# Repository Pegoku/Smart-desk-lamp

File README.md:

# Smart Desk Lamp

This is a home assistant controlled CWWW desk lamp with capacitive touch buttons, made with ESPHome and ESP32-C3.

## Why I made it?

I made this project as I wanted to learn more about capacitive touch sensors and how to use them with ESPHome. I also wanted to make a simple desk lamp that could be controlled with Home Assistant.

## Features

- Capacitive touch buttons to control the brightness and color temperature of the LEDs.
- Home Assistant integration.

## Images

Final Build:

<details>
  <summary>Case/Assembly</summary>

</details>
<details>
  <summary>Main Schematic</summary>

</details>
<details>
  <summary>Main PCB</summary>

</details>

</details>
<details>
  <summary>LED Schematic</summary>

</details>
<details>
  <summary>LED PCB</summary>

</details>

## BOM

| Index | Part Number                        | What the item is for in your project | Description                         | Pack Quantity | ID                                                    | Unit Price | Total Price | Total (incl. VAT shipping, etc) |
| ----- | ---------------------------------- | ------------------------------------ | ----------------------------------- | ------------- | ----------------------------------------------------- | ---------- | ----------- | ------------------------------- |
| 1     | IQS7222A001QNR                     | Capacitive sensor                    | 9 CHANNEL MUTUAL / 8 SELF-CAPAC     | 2             | 1790-IQS7222A001QNRCT-ND                              | 0.82       | 1.64        | ~140$                            |
| 2     | ESP32-C3-WROOM-02-H4               | MCU                                  | RF TXRX MOD BT WIFI PCB TH SMD      | 1             | 1965-ESP32-C3-WROOM-02-H4CT-ND                        | 3.51       | 3.51        |                                 |
| 3     | IRM-20-24                          | PSU                                  | AC/DC CONVERTER 24V 22W             | 1             | 1866-3040-ND                                          | 9.20       | 9.20        |                                 |
| 4     | AP63203WU-7                        | 3.3V buck                            | IC REG BUCK 3.3V 2A TSOT23-6        | 2             | AP63203WU-7DICT-ND                                    | 0.71       | 1.42        |                                 |
| 5     | AL5802-7                           | Led driver                           | IC LED DRVR LIN PWM 120MA SOT26     | 5             | AL5802-7DICT-ND                                       | 0.23       | 1.15        |                                 |
| 6     | 2N7002                             | mosfet to drive the led drivers      | MOSFET N-CH 60V 280MA SOT23-3       | 3             | 4878-2N7002CT-ND                                      | 0.12       | 0.36        |                                 |
| 7     | GW JTLPS1.CM-HNKK-XX510-1-150-R33  | 2200K led                            | LED DURIS E2835 WHT 2200K 2835      | 10            | 475-GWJTLPS1.CM-HNKK-XX510-1-150-R33CT-ND             | 0.067      | 0.67        |                                 |
| 8     | GW JTLPS1.CM-JNKN-XX51-1-150-R33   | 6500K led                            | LED DURIS E2835 WHITE 6500K 2835    | 10            | 475-GWJTLPS1.CM-JNKN-XX51-1-150-R33CT-ND              | 0.067      | 0.67        |                                 |
| 9     | SRR5018-3R9Y                       | inductor                             | FIXED IND 3.9UH 2A 55 MOHM SMD      | 2             | 118-SRR5018-3R9YCT-ND                                 | 0.64       | 1.28        |                                 |
| 10    | 12mm LED Gooseneck                 | 12mm LED Gooseneck                   | 30 cm silver, Outer M10 – Outer M10 | 1             | https://es.aliexpress.com/item/1005007938186623.html  | 11.50      | 11.50       |                                 |
| 11    | 703W-00/53                         | Power Connector                      | PWR ENT RCPT IEC320-C14 PNL SLDR    | 1             | Q219-ND                                               | 1.54       | 1.54        |                                 |
| 12    | MF72-005D7                         | Inrush current limiter               | ICL 5 Ω 20% 2A 9 mm                 | 2             | 317-1148-ND                                           | 0.43       | 0.86        |                                 |
| 13    | M3x30 mm 4762                      | M3x30 mm 4762                        | M3x30 mm 4762                       | 1             | https://www.aliexpress.com/item/1005006453614010.html | 3.105      | 3.105       |                                 |
| 14    | M10 nut                            | M10 nut                              | M10 nut                             | 1             | https://www.aliexpress.com/item/1005007593861199.html | 3.0935     | 3.0935      |                                 |
| 15    | Soldering iron heatset insert tips | Soldering iron heatset insert tips   | Soldering iron heatset insert tips  | 1             | https://www.aliexpress.com/item/1005008493831823.html | 21.3785    | 21.3785     |                                 |
| 16    | M3x6 mm 4762                       | M3x6 mm 4762                         | M3x6 mm 4762                        | 1             | https://www.aliexpress.com/item/1005006453614010.html | 2.139      | 2.139       |                                 |
| 17    | Wood Filament                      | Wood Filament                        | Wood Filament                       | 0             | https://www.aliexpress.com/item/1005006685394618.html | 38.1685    | 0           |                                 |
| 18    | 30 cm JST XH 4P                    | 30 cm JST XH 4P                      | 30 cm JST XH 4P                     | 1             | https://www.aliexpress.com/item/1005008319201640.html | 2.5645     | 2.5645      |                                 |
| 19    | CL10A104KA8NNNC                    | Passive                              | CAP CER 0.1 µF 25 V X5R 0603        | 10            | 1276-1857-1-ND                                        | 0.028      | 0.28        |                                 |
| 20    | CL10A475KQ8NNNC                    | Passive                              | CAP CER 4.7 µF 6.3 V X5R 0603       | 10            | 1276-1045-1-ND                                        | 0.008      | 0.08        |                                 |
| 21    | CL10A225KQ8NNNC                    | Passive                              | CAP CER 2.2 µF 6.3 V X5R 0603       | 10            | 1276-1183-1-ND                                        | 0.032      | 0.32        |                                 |
| 22    | CL10A226MQ8NRNC                    | Passive                              | CAP CER 22 µF 6.3 V X5R 0603        | 5             | 1276-1193-1-ND                                        | 0.22       | 1.10        |                                 |
| 23    | CL10A104KA8NNNC                    | Passive                              | CAP CER 0.1 µF 25 V X5R 0603        | 10            | 1276-1857-1-ND                                        | 0.028      | 0.28        |                                 |
| 24    | CL05C101JB5NNNC                    | Passive                              | CAP CER 100 pF 50 V C0G/NP0 0402    | 10            | 1276-1025-1-ND                                        | 0.003      | 0.03        |                                 |
| 25    | 61300411121                        | Passive                              | CONN HEADER VERT 4POS 2.54 mm       | 2             | 732-5317-ND                                           | 0.17       | 0.34        |                                 |
| 26    | CRCW0603470MJPEAHR                 | Passive                              | RES SMD 470 MΩ 5% 1/10 W 0603       | 10            | 541-470MAHCT-ND                                       | 0.151      | 1.51        |                                 |
| 27    | RC0603FR-074K7L                    | Passive                              | RES 4.7 KΩ 1% 1/10 W 0603           | 10            | 311-4.70KHRCT-ND                                      | 0.009      | 0.09        |                                 |
| 28    | RC0603FR-071KL                     | Passive                              | RES 1 KΩ 1% 1/10 W 0603             | 10            | 311-1.00KHRCT-ND                                      | 0.009      | 0.09        |                                 |
| 29    | RC0603FR-0710KL                    | Passive                              | RES 10 KΩ 1% 1/10 W 0603            | 10            | 311-10.0KHRCT-ND                                      | 0.009      | 0.09        |                                 |
| 30    | PTS815SJM250SMTRLFS                | Esp32 buttons                        | SWITCH TACTILE SPST-NO 0.05 A 12 V  | 4             | CKN12215-1-ND                                         | 0.22       | 0.88        |                                 |
| 31    | PCB                                | PCB                                  | PCBs + stencil                      | 1             | jlcpcb.com                                            | 53.03      | 53.03       |                                 |
| 32    | ERJ-6GEY0R00V                      | 0 ohm jumper                         | RES SMD 0 OHM JUMPER 1/8W 0805      | 20            | P0.0ACT-ND                                            | 0.02360    | 0.59        |                                 |

## Configuration

Remember to set your secrets in [secrets.yaml](Code/secrets.example.yaml).

All firmware configuration lives in [code.yaml](Code/code.yaml):
PS: This configuration is for reference only, The final configuration will be for the ESP32-S2. You'll also have to configure the devices you want to control in Home Assistant.

```yaml
esphome:
  name: desklight
  friendly_name: desklight

esp32:
  board: esp32-c3-devkitm-1
  framework:
    type: arduino

# Enable logging
logger:

# Enable Home Assistant API
api:
  encryption:
    key: !secret api_key

ota:
  - platform: esphome
    password: !secret ota_password

wifi:
  ssid: !secret wifi_ssid
  password: !secret wifi_password

  # Enable fallback hotspot (captive portal) in case wifi connection fails
  ap:
    ssid: "desklight Fallback Hotspot"
    password: "wHjqyQOLnaPa"

i2c:
  sda: GPIO6
  scl: GPIO7
  frequency: 800kHz
  scan: true

mpr121:
  id: mpr121_component
  address: 0x5A
  touch_debounce: 1
  release_debounce: 1
  touch_threshold: 10
  release_threshold: 7

binary_sensor:
  - platform: mpr121
    id: touch_key0
    channel: 0
    name: "Touch Key 0"
    touch_threshold: 12
    release_threshold: 6

light:
  - platform: cwww
    name: "Livingroom Lights"
    cold_white: WLight
    warm_white: CLight
    cold_white_color_temperature: 6500 K
    warm_white_color_temperature: 2200 K
    constant_brightness: true

output:
  - platform: ledc
    id: WLight
    pin: GPIO4
    frequency: 1000 Hz
  - platform: ledc
    id: CLight
    pin: GPIO5
    frequency: 1000 Hz

captive_portal:
```

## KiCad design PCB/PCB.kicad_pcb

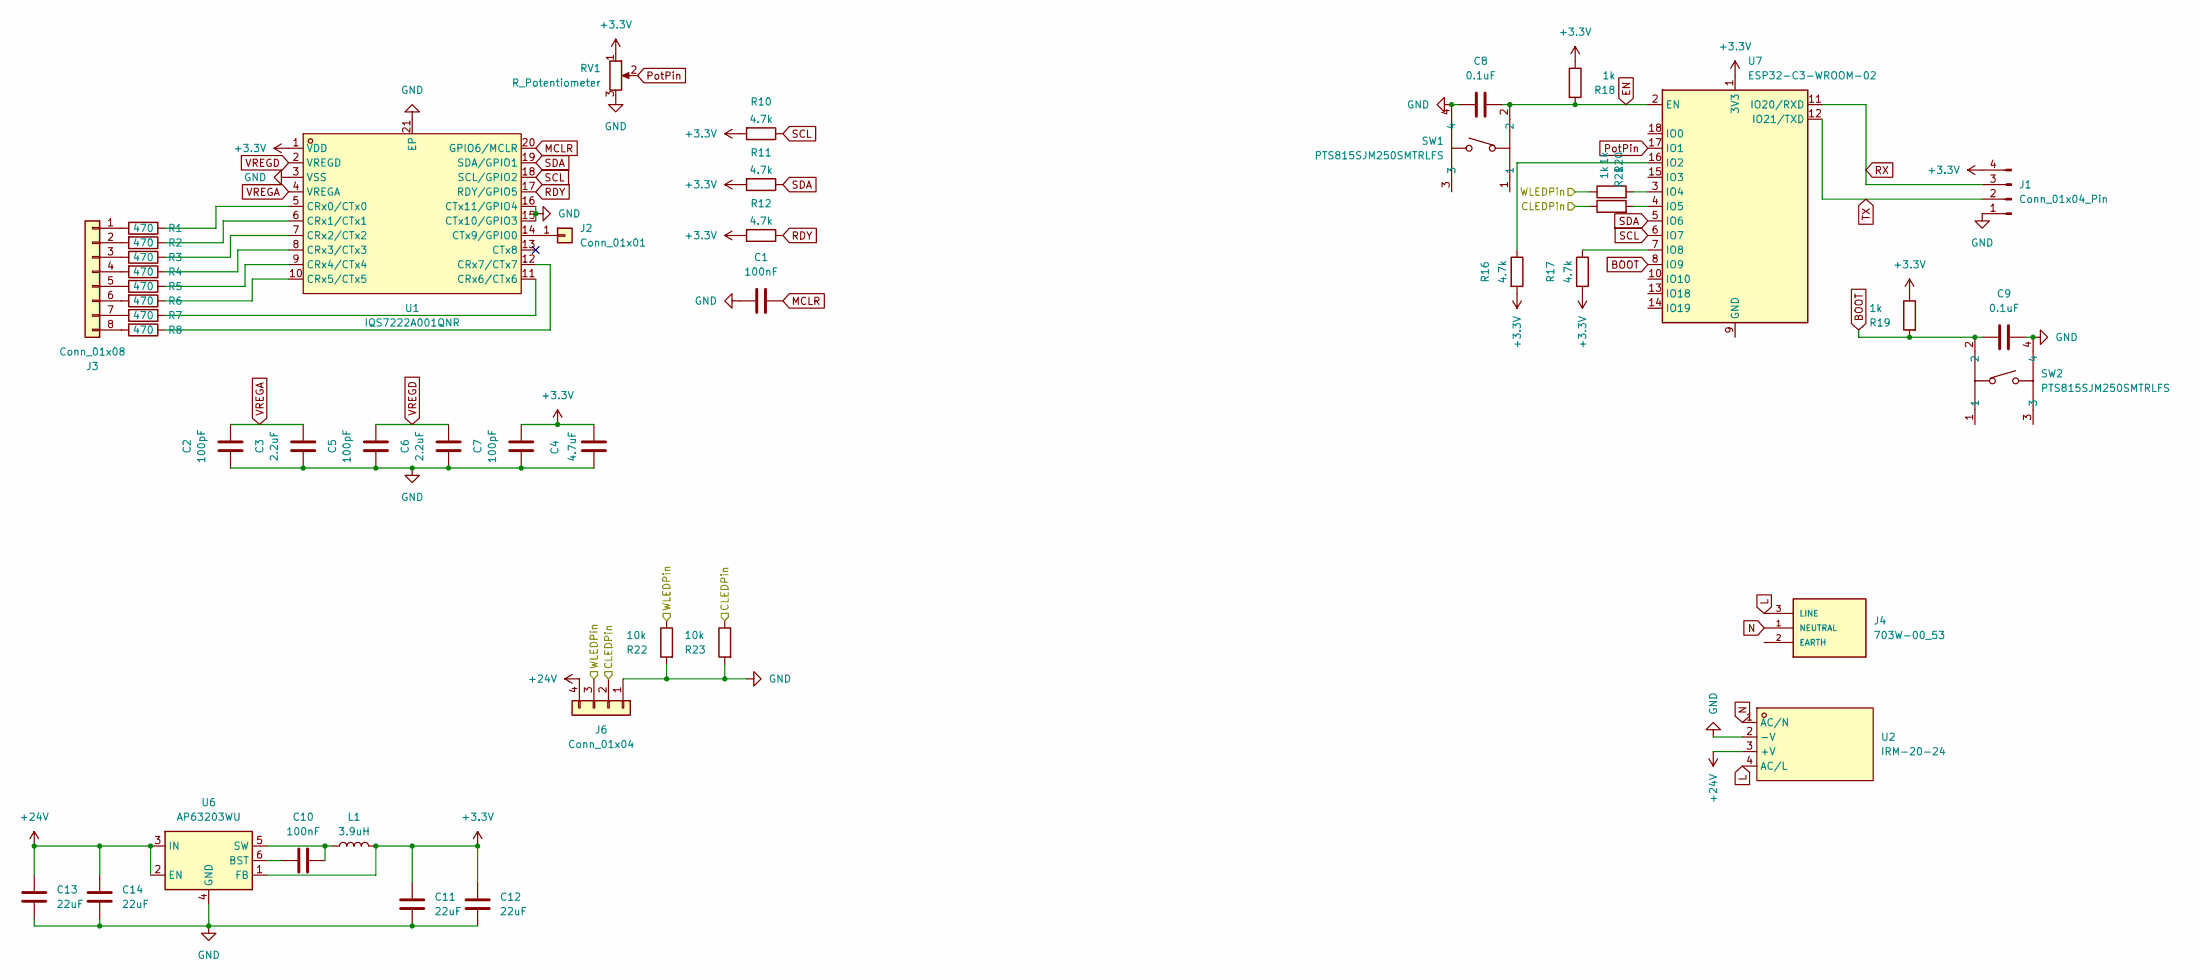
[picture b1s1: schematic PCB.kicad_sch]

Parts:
C1, C10: 100nF; C_0603_1608Metric
C2, C5, C7: 100pF; C_0603_1608Metric
C3, C6: 2.2uF; C_0603_1608Metric
C4: 4.7uF; C_0603_1608Metric
C8, C9: 0.1uF; C_0603_1608Metric
C11, C12, C13, C14: 22uF; C_0603_1608Metric
J1: Conn_01x04_Pin; PinHeader_1x04_P2.54mm_Vertical
J2: Conn_01x01; PinHeader_1x01_P2.54mm_Vertical
J3: Conn_01x08; TouchSlider-8_50x20mm
J4: 703W-00_53; QUALTEK_703W-00_53
J6: Conn_01x04; JST_XH_B4B-XH-AM_1x04_P2.50mm_Vertical
L1: 3.9uH; IND-SMD_L5.8-W5.8
R1, R2, R3, R4, R5, R6, R7, R8: 470; R_0603_1608Metric
R10, R11, R12, R16, R17: 4.7k; R_0603_1608Metric
R18, R19, R20, R21: 1k; R_0603_1608Metric
R22, R23: 10k; R_0603_1608Metric
RV1: R_Potentiometer; PinHeader_1x03_P2.54mm_Horizontal
SW1, SW2: PTS815SJM250SMTRLFS; KEY-SMD_4P-L4.2-W3.25-P2.15-TL; LCSC Part C2689510
U1: IQS7222A001QNR; WQFN-20_L3.0-W3.0-P0.40-BL-EP1.7; LCSC Part C3827627
U2: IRM-20-24; PWRM-TH_IRM-20-24; LCSC Part C194964
U6: AP63203WU; TSOT-23-6
U7: ESP32-C3-WROOM-02

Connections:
+3.3V: C4.2, C7.2, C11.2, C12.2, J1.4, L1.2, R10.2, R11.2, R12.2, R16.2, R17.2, R18.1, R19.1, RV1.1, U1.1 (VDD), U6.1 (FB), U7.1 (3V3)
+24V: C13.2, C14.2, J6.4, U2.3 (+V), U6.2 (EN), U6.3 (IN)
/Main PCB/CLEDPin: J6.2, R21.1, R23.1
/Main PCB/WLEDPin: J6.3, R20.1, R22.1
BOOT: C9.1, R19.2, SW2.2, U7.8 (IO9)
EN: C8.1, R18.2, SW1.2, U7.2 (EN)
GND: C1.1, C2.1, C3.1, C4.1, C5.1, C6.1, C7.1, C8.2, C9.2, C11.1, C12.1, C13.1, C14.1, J1.1, J6.1, R22.2, R23.2, RV1.3, SW1.4, SW2.4, U1.3 (VSS), U1.15 (CTx10/GPIO3), U1.16 (CTx11/GPIO4), U1.21 (EP), U2.2 (-V), U6.4 (GND)
L: J4.3 (LINE), U2.4 (AC/L)
MCLR: C1.2, U1.20 (GPIO6/MCLR)
N: J4.1 (NEUTRAL), U2.1 (AC/N)
unnamed: J2.1, U1.14 (CTx9/GPIO0)
unnamed: J3.1, R1.2
unnamed: J3.2, R2.2
unnamed: J3.3, R3.2
unnamed: J3.4, R4.2
unnamed: J3.5, R5.2
unnamed: J3.6, R6.2
unnamed: J3.7, R7.2
unnamed: J3.8, R8.2
unnamed: R1.1, U1.5 (CRx0/CTx0)
unnamed: R2.1, U1.6 (CRx1/CTx1)
unnamed: R3.1, U1.7 (CRx2/CTx2)
unnamed: R4.1, U1.8 (CRx3/CTx3)
unnamed: R5.1, U1.9 (CRx4/CTx4)
unnamed: R6.1, U1.10 (CRx5/CTx5)
unnamed: R7.1, U1.11 (CRx6/CTx6)
unnamed: R8.1, U1.12 (CRx7/CTx7)
unnamed: C10.1, U6.6 (BST)
unnamed: C10.2, L1.1, U6.5 (SW)
unnamed: U7.9 (GND), U7.19 (GND)
unnamed: R16.1, U7.16 (IO2)
unnamed: R20.2, U7.3 (IO4)
unnamed: R21.2, U7.4 (IO5)
unnamed: R17.1, U7.7 (IO8)
PotPin: RV1.2, U7.17 (IO1)
RDY: R12.1, U1.17 (RDY/GPIO5)
RX: J1.3, U7.11 (IO20/RXD)
SCL: R10.1, U1.18 (SCL/GPIO2), U7.6 (IO7)
SDA: R11.1, U1.19 (SDA/GPIO1), U7.5 (IO6)
TX: J1.2, U7.12 (IO21/TXD)
VREGA: C2.2, C3.2, U1.4 (VREGA)
VREGD: C5.2, C6.2, U1.2 (VREGD)

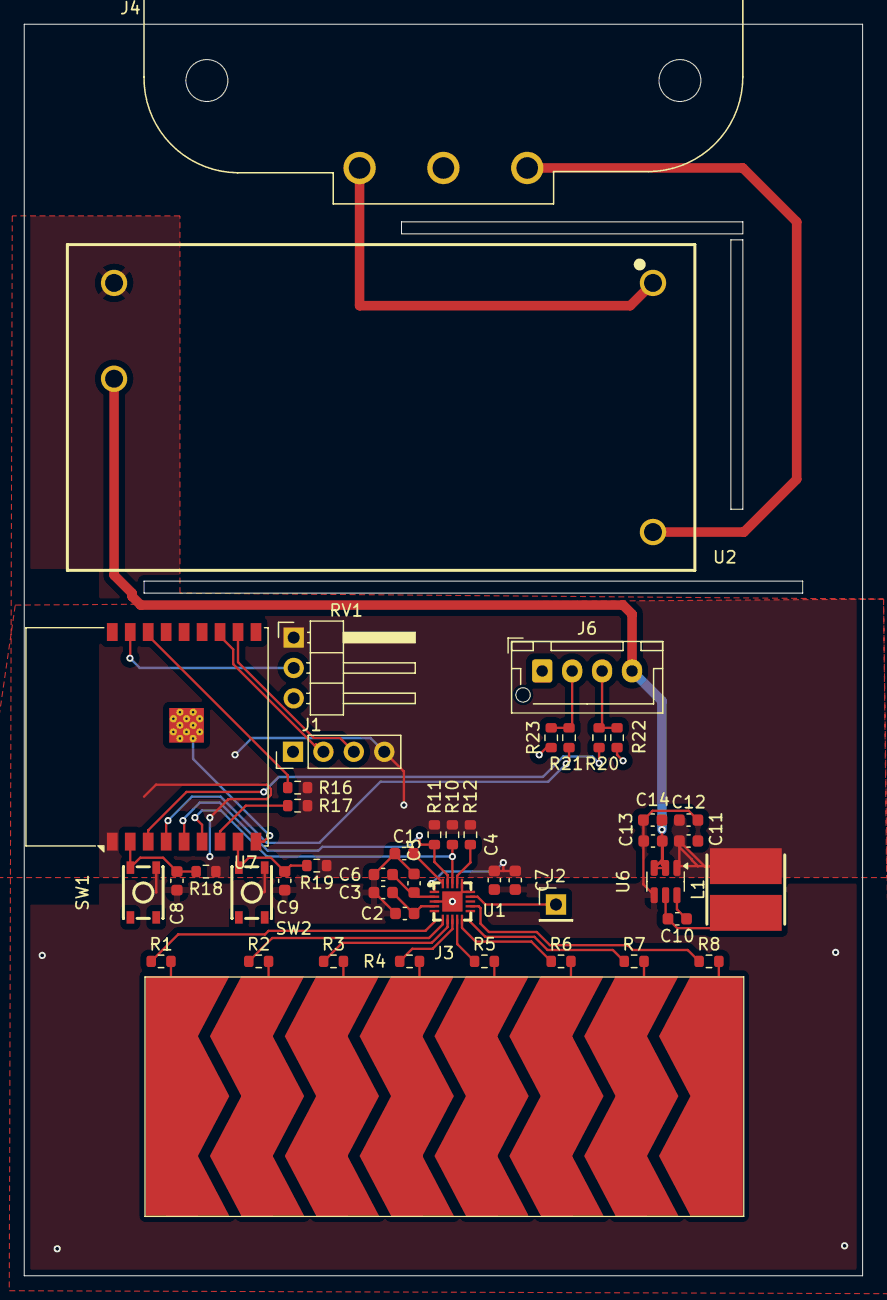
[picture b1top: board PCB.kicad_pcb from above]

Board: 2 copper layers, 70.0 x 104.5 mm, 46 parts (0 on the bottom side), 42 nets.

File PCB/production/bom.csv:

Designator,Footprint,Quantity,Value,LCSC Part #
"C1, C10",0603,2,100nF,
"C11, C12, C13, C14",0603,4,22uF,
"C2, C5, C7",0603,3,100pF,
"C3, C6",0603,2,2.2uF,
C4,0603,1,4.7uF,
"C8, C9",0603,2,0.1uF,
J1,PinHeader_1x04_P2.54mm_Vertical,1,Conn_01x04_Pin,
J2,PinHeader_1x01_P2.54mm_Vertical,1,Conn_01x01,
J3,TouchSlider-8_50x20mm,1,Conn_01x08,
J4,QUALTEK_703W-00_53,1,703W-00_53,
J6,JST_XH_B4B-XH-AM_1x04_P2.50mm_Vertical,1,Conn_01x04,
L1,IND-SMD_L5.8-W5.8,1,3.9uH,
"R1, R2, R3, R4, R5, R6, R7, R8",0603,8,470,
"R10, R11, R12, R16, R17",0603,5,4.7k,
"R18, R19, R20, R21",0603,4,1k,
"R22, R23",0603,2,10k,
RV1,PinHeader_1x03_P2.54mm_Horizontal,1,R_Potentiometer,
"SW1, SW2",KEY-SMD_4P-L4.2-W3.25-P2.15-TL,2,PTS815SJM250SMTRLFS,C2689510
U1,WQFN-20_L3.0-W3.0-P0.40-BL-EP1.7,1,IQS7222A001QNR,C3827627
U2,PWRM-TH_IRM-20-24,1,IRM-20-24,C194964
U6,TSOT-23-6,1,AP63203WU,
U7,ESP32-C3-WROOM-02,1,ESP32-C3-WROOM-02,

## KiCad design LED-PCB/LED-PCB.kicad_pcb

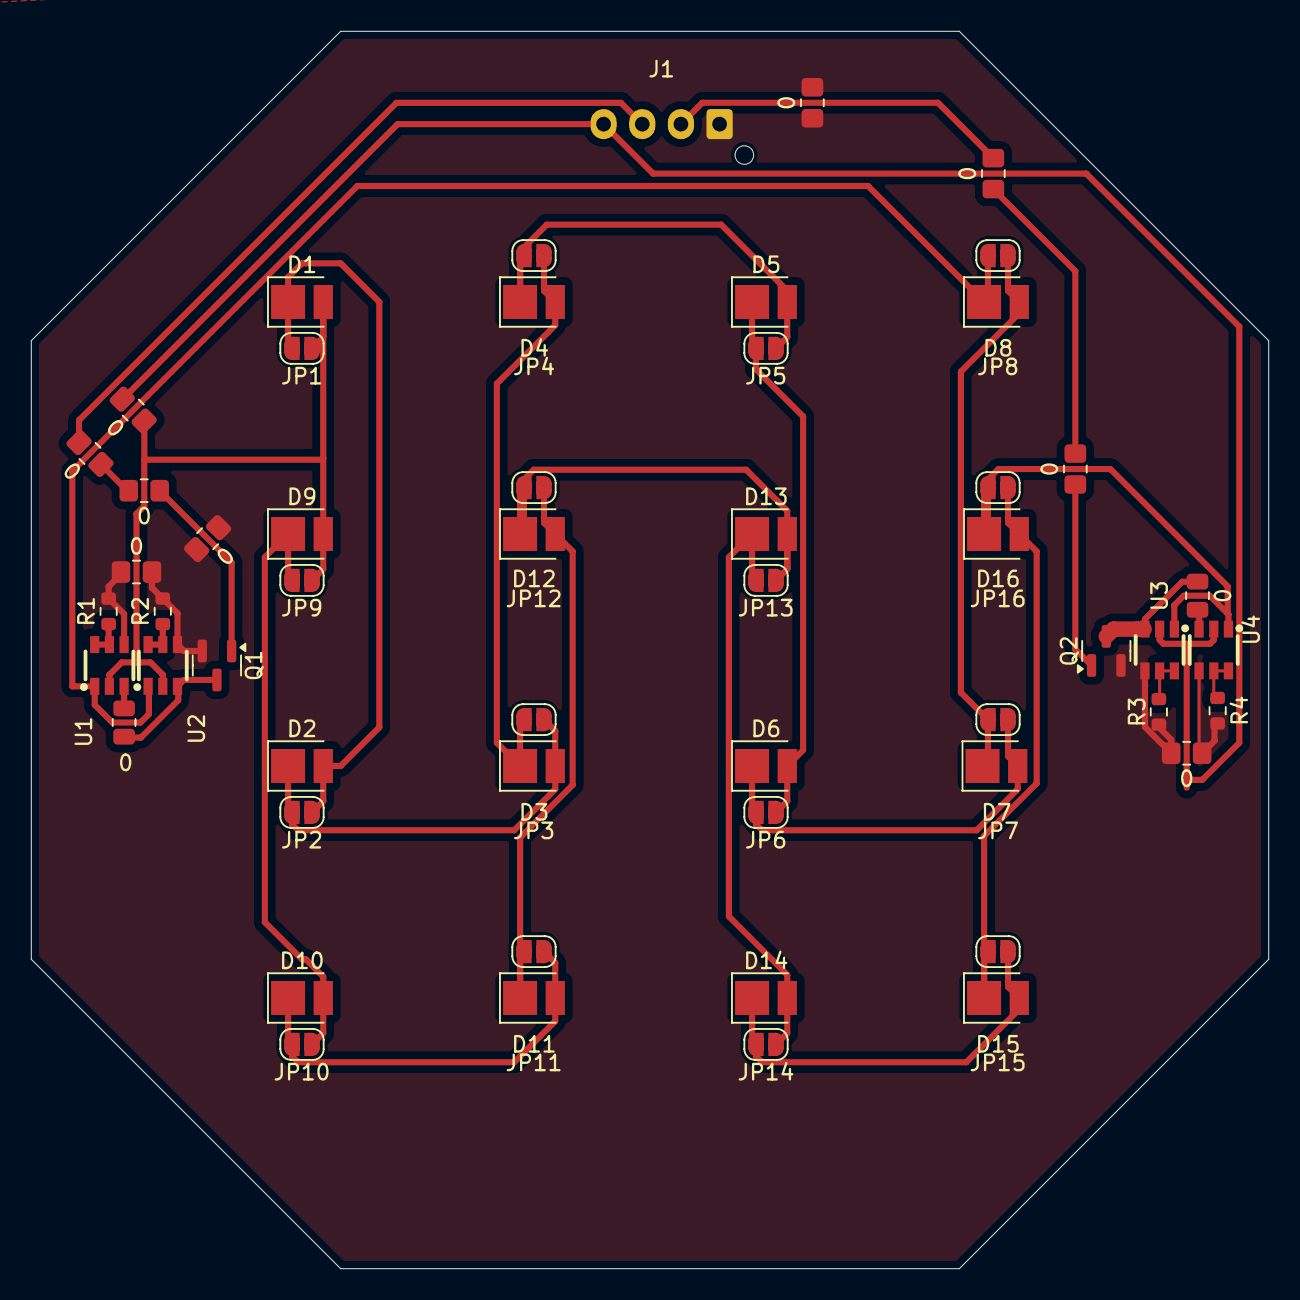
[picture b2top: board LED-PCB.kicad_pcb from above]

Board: 2 copper layers, 80.0 x 80.0 mm, 54 parts (1 on the bottom side), 26 nets.

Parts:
0, 0#8: 0; R_0805_2012Metric
0#2, 0#3, 0#4, 0#5, 0#6, 0#7, 0#9, 0#10, 0#11: R_0805_2012Metric_Pad1.20x1.40mm_HandSolder
D1, D2, D3, D4, D5, D6, D7, D8: LEDW; LED_PLCC_2835
D9, D10, D11, D12, D13, D14, D15, D16: LEDC; LED_PLCC_2835
J1: Conn_01x04; JST_XH_B4B-XH-AM_1x04_P2.50mm_Vertical
JP1, JP2, JP3, JP4, JP5, JP6, JP7, JP8, JP9, JP10, JP11, JP12, JP13, JP14, JP15, JP16: SolderJumper_2_Open; SolderJumper-2_P1.3mm_Open_RoundedPad1.0x1.5mm
Q1, Q2: 2N7002; SOT-23
R1, R2, R3, R4: 9.1; R_0603_1608Metric
U1, U2, U3, U4: AL5802-7; SOT-23-6_L2.9-W1.6-P0.95-LS2.8-BR

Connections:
+24V: 0#4.1, 0#4.2, D1.2 (A), D9.2 (A), J1.4, JP1.1 (A), JP9.1 (A), U1.2, U2.2, U3.2, U4.2
/CLEDPin: 0#2.1, 0#2.2, 0#3.1, 0#3.2, J1.2, Q2.1 (G)
/WLEDPin: 0#6.1, 0#6.2, 0#11.1, 0#11.2, J1.3, Q1.1 (G)
GND: 0#5.1, 0#5.2, 0#7.1, 0#7.2, 0#9.1, 0#9.2, 0#10.1, 0#10.2, J1.1, Q1.2 (S), Q2.2 (S), R1.2, R2.2, R3.2, R4.2, U1.4, U2.4, U3.4, U4.4
unnamed: D1.1 (K), D2.2 (A), JP1.2 (B), JP2.1 (A)
unnamed: D2.1 (K), D3.2 (A), JP2.2 (B), JP3.1 (A)
unnamed: D3.1 (K), D4.2 (A), JP3.2 (B), JP4.1 (A)
unnamed: D4.1 (K), D5.2 (A), JP4.2 (B), JP5.1 (A)
unnamed: D5.1 (K), D6.2 (A), JP5.2 (B), JP6.1 (A)
unnamed: D6.1 (K), D7.2 (A), JP6.2 (B), JP7.1 (A)
unnamed: D7.1 (K), D8.2 (A), JP7.2 (B), JP8.1 (A)
unnamed: D8.1 (K), JP8.2 (B), U1.1, U2.1
unnamed: D9.1 (K), D10.2 (A), JP9.2 (B), JP10.1 (A)
unnamed: D10.1 (K), D11.2 (A), JP10.2 (B), JP11.1 (A)
unnamed: D11.1 (K), D12.2 (A), JP11.2 (B), JP12.1 (A)
unnamed: D12.1 (K), D13.2 (A), JP12.2 (B), JP13.1 (A)
unnamed: D13.1 (K), D14.2 (A), JP13.2 (B), JP14.1 (A)
unnamed: D14.1 (K), D15.2 (A), JP14.2 (B), JP15.1 (A)
unnamed: D15.1 (K), D16.2 (A), JP15.2 (B), JP16.1 (A)
unnamed: D16.1 (K), JP16.2 (B), U3.1, U4.1
unnamed: 0#8.1, 0#8.2, Q1.3 (D), U1.3, U2.3
unnamed: 0.1, 0.2, Q2.3 (D), U3.3, U4.3
unnamed: R1.1, U1.5, U1.6
unnamed: R2.1, U2.5, U2.6
unnamed: R3.1, U3.5, U3.6
unnamed: R4.1, U4.5, U4.6

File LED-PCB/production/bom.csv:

Designator,Footprint,Quantity,Value,LCSC Part #
"0_11, 0_10, 0_9, 0_7, 0_6, 0_5, 0_4, 0_2, 0",0805,9,R_0805_2012Metric_Pad1.20x1.40mm_HandSolder,
"0_8, 0_3",0805,2,0,
"D1, D2, D3, D4, D5, D6, D7, D8",LED_PLCC_2835,8,LEDW,
"D10, D11, D12, D13, D14, D15, D16, D9",LED_PLCC_2835,8,LEDC,
J1,JST_XH_B4B-XH-AM_1x04_P2.50mm_Vertical,1,Conn_01x04,
"Q1, Q2",SOT-23,2,2N7002,
"R1, R2, R3, R4",0603,4,9.1,
"U1, U2, U3, U4",SOT-23-6_L2.9-W1.6-P0.95-LS2.8-BR,4,AL5802-7,C129160

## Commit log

2025-06-18 code
2025-06-18 add images + readme
2025-06-18 ready for highway
2025-07-31 first working code (example) and config
2025-08-04 working code
2025-08-06 finish project
2025-08-06 Add Final Build image to README.md
2025-08-06 Create LICENSE
